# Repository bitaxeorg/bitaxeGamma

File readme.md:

```
Open Source is Intrinsic to Bitcoin
```
# The bitaxeGamma
bitaxe is a fully open source Bitcoin ASIC miner aimed at decentralizing mining. bitaxeGamma is the 5th major revision of the bitaxe that now includes the BM1370 ASIC from the Antminer S21 Pro

## Goals
- **Easy**: Just plug it in and mine Bitcoin over WiFi. No external computer needed.
- **Practical**: low cost, low noise, low power, low maintenance. You can run this at home.
- **ASIC Power**: High efficiency and hashrate, based on the latest and greatest Application Specific Integrated Circuits.
- **Versatile**: Mine to any StratumV1 pool, Lottery mine, Solo mine, Or hack it to do whatever you want.
- **Bitcoin Ethos**: Fully open source, permissionless and decentralized to support the worldwide freedom money.

## ASIC
At the heart of the bitaxeGamma is a BM1370 Bitcoin mining ASIC from the Antminer S21 Pro from Bitmain. It's not open source.

- Bitmain claims the BM1370 has 15 J/TH efficiency. We can get pretty close to that with the BitaxeGamma
- The Antminer S21 Pro has a nominal hashrate of 234 TH/s. There are 3 hashboards with 65 chips each, for a total of 195 chips. The bitaxeGamma has a single one of these chips. That means _about_ 1.2 TH/s per bitaxeGamma. Initial testing looks good!
- The BM1370 is brand new and isn't available individually yet. The best place to get these chips is right out of a S21 Pro.
- The BM1370 has a different footprint and pinout from the BM1368, BM1366, BM1397 and BM1387 in previous bitaxe.

## Current Status
- BitaxeGamma 600 is working well and has been released!
- In addition to higher hashrate, the Gamma also uses more power. Please pay attention to hash frequency and voltage settings as it's much easier to overheat, especially when using the stock heatsink and fan.
- BM1370 firmware support has been added to [esp-miner](https://github.com/skot/esp-miner)
- Be sure to check the [HW issues](https://github.com/skot/bitaxe/issues) for known bugs, reworks and errata.
- This is an _advanced_ build! You can do it, but if you're not looking for a project, it might be best to buy one pre-assembled from one of the [many sellers](https://bitaxe.org/legit.html). Check [Skot's method](assembly.md) of hand assembling PCBs.

## PCB Hardware
This repo contains all of the design files for the PCB. [KiCAD](https://www.kicad.org/) software is used. There is a BOM file for all of the components that get soldered to the PCB. 

- Order PCBs from your favorite PCB shop, like [JLCPCB](https://jlcpcb.com), [SeeedStudio](https://www.seeedstudio.com/fusion_pcb.html), or [PCBWay](https://www.pcbway.com)
    - Gerbers are in the `Manufacturing Files` dir. PCBs are 4-layer, 6mil trace/space and 0.3mm hole compatible. 1oz outer / 0.5oz inner layer thickness works well.
    - Make sure to order stencils too. These are the "paste" layers in the gerbers folder. one for top and one for bottom.
- All PCB parts except the ASIC are available from [DigiKey](https://www.digikey.com/en/products) and others. You can find Digikey part numbers on the DK tab of the BOM

## Extra Hardware
There are a few other hardware components that are needed for a complete bitaxe.

- **Heatsink**
	- [40x40mm heatsink and 5V fan](https://www.aliexpress.com/item/2251832861666365.html) from a random AliExpress seller. The fans are crap, but the heatsinks are good.  
- **Fan**
	- You **must** have active cooling on the bitaxe. The heatsink alone is not enough.
	- The Bitaxe has a connector for a 4pin, 5V PWM fan. 40mm square, 20mm thick fans work nicely with the suggested heatsink. Make sure to get a 5V fan! 12V spin, but slowly overheating your Bitaxe..
	- Upgrade your fan with the [Noctua NF-A4x10](https://noctua.at/en/nf-a4x10-5v-pwm) 5V 4-Pin fan for a much more pleasant experience.
- **Thermal compound**
	- Use a good quality thermal compound between the heatsink and ASIC. [Thermal Grizzly Kryonaut](https://www.amazon.com/Thermal-Grizzly-Kryonaut-Grease-Paste/dp/B011F7W3LU) has been known to work well.  
- **Display**
	- Supports 0.91" SSD1306-based I2C OLED Module. [Example Amazon seller](https://www.amazon.com/gp/product/B08ZY4YBHL). Make sure to get the male pins to interface with the Bitaxe PCB. 
- **Power Supply**
	- **5V DC Only!** Anything else will damage the Bitaxe. Be careful and double-check your power supply is 5V. Many other voltage power supplies use the same connector.
	- The power supply needs to supply in excess of 4A (20W) and not drop below 5V. Often times you have to use a power supply rated for 25-30W to get this!
 		- The [Meanwell GST60A05-P1J](https://www.digikey.com/en/products/detail/mean-well-usa-inc/GST60A05-P1J/7703709) at 30 Watts is the cadillac of 5V PSUs and is working well with the Gamma.  
	- The bitaxe uses a 5.5x2.1mm, center-positive barrel jack. 5.5x2.5mm plugs have been known to work.
- **Stand**
	- The PCB has corner mounting holes. You're going to want a stand to mount your Bitaxe. Many excellent 3D printed designs are available.

## Firmware
- The [ESP-Miner](https://github.com/skot/ESP-Miner) has initial support for the BM1370 ASIC. Improvements are ongoing.

### ESP32 Programming Requirements
- As of the bitaxeUltra, all ESP32 programming is done through a USB-C cable and connector on the bitaxe. See [ESP-Miner](https://github.com/skot/ESP-Miner) for more details.

## More Information
- Project page at [bitaxe.org](https://bitaxe.org)
- [Open Source Miners United](discord.gg/osmu) Discord chat
- [building.md](building.md) for PCB ordering tips
- [assembly.md](assembly.md) for assembly tips

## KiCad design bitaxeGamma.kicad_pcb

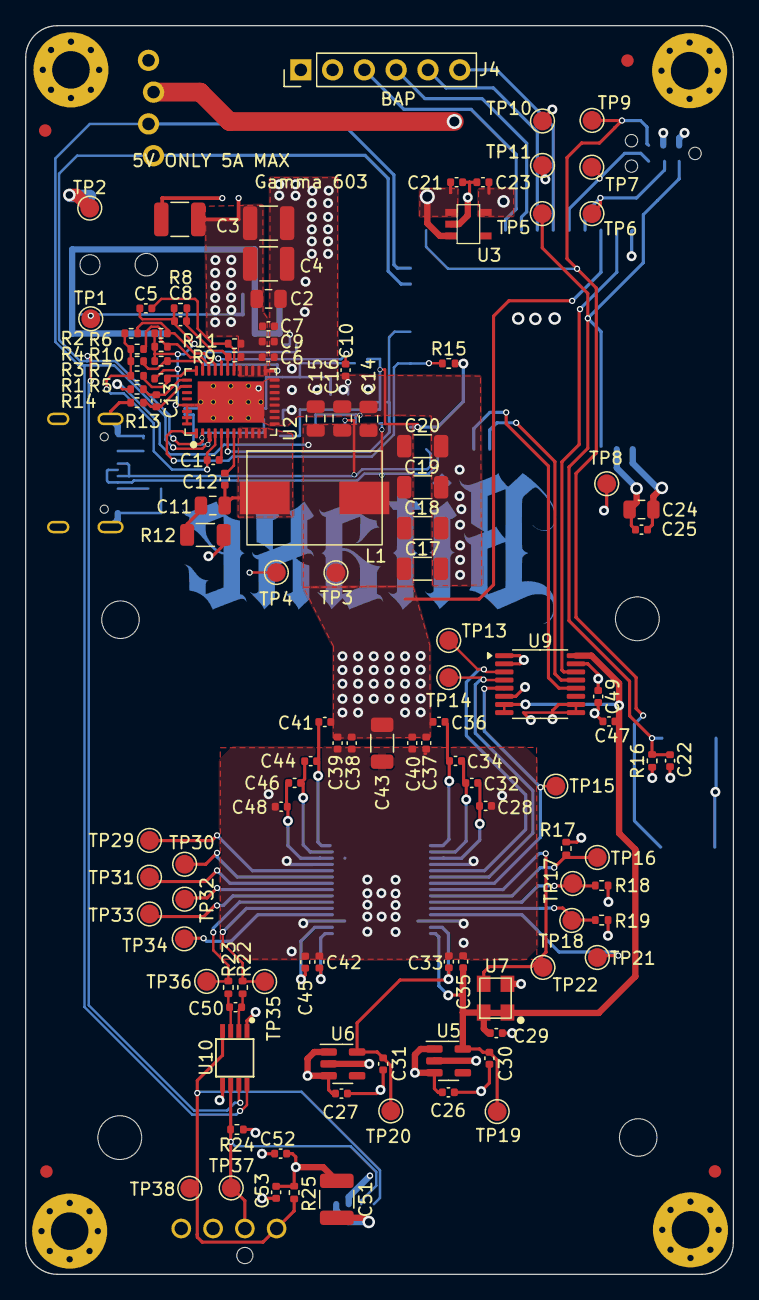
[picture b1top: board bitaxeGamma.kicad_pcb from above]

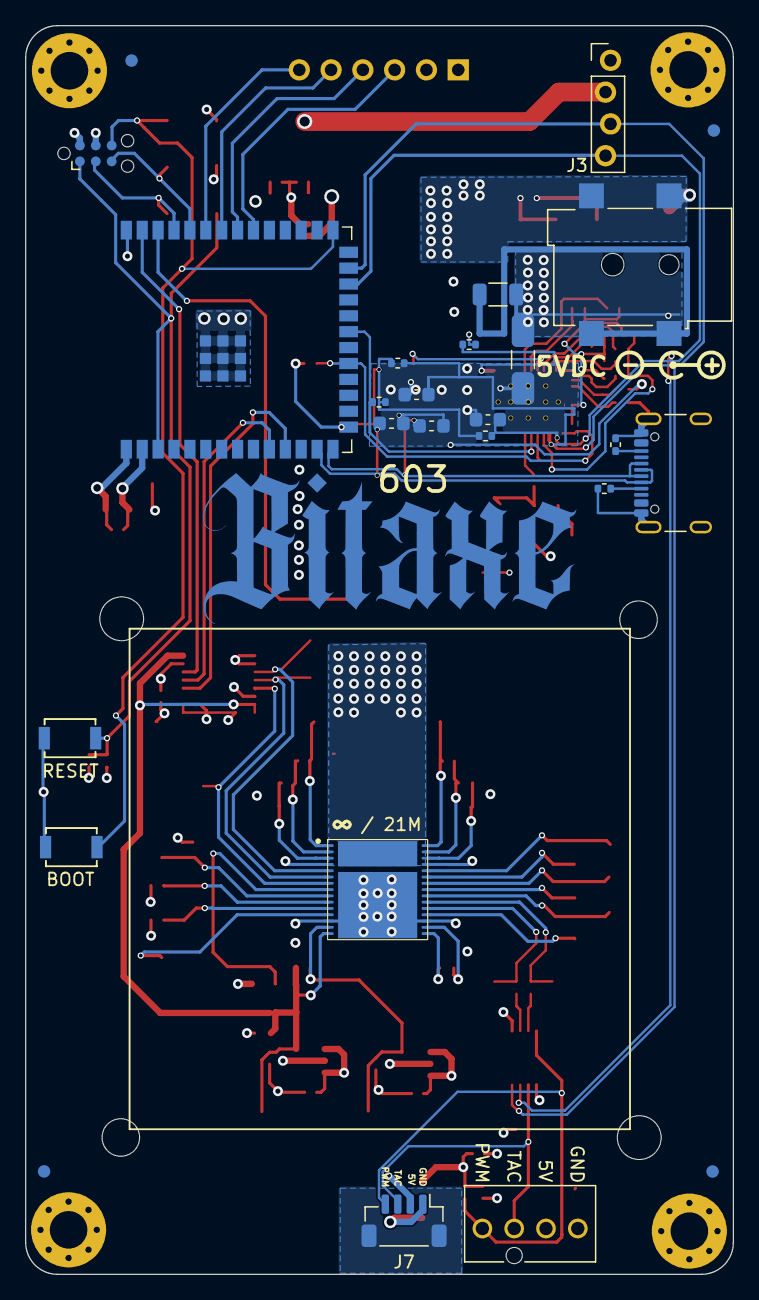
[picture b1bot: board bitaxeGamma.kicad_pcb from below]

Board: 4 copper layers, 56.5 x 99.8 mm, 157 parts (27 on the bottom side), 67 nets.

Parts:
C1, C5, C7, C21, C22, C23, C26, C27, C28, C30, C31, C32, C33, C34, C35, C36, C39, C40, C41, C42, C44, C45, C46, C48: 1uF; C_0402_1005Metric
C2, C24: 10uF; C_0805_2012Metric
C3, C4, C51: 47uF; C_1210_3225Metric
C6: 4700pF; C_0402_1005Metric
C8, C12, C25, C29, C37, C38, C47, C49, C52, C53, C62: 0.1uF; C_0402_1005Metric
C9: 2200pF; C_0402_1005Metric
C10: 4.7uF; C_0402_1005Metric
C11: 1000pF; C_0805_2012Metric
C13: 100pF; C_0402_1005Metric
C14, C15, C16: 22uF; C_0805_2012Metric
C17, C18, C19, C20, C43: 100uF; C_1206_3216Metric
C50: 470pF; C_0402_1005Metric
C60: 100uF; C_1210_3225Metric
D1: SMAJ5.0A; D_SMA
D2, D5: PESD5V0S1BL; D_SOD-323
D3, D4: PESD3V3S1BL; D_SOD-323
F1: 5A; Fuse_1206_3216Metric
FID1, FID2, FID3, FID4, FID5, FID6, FID7, FID8: Fiducial; Fiducial_1mm_Mask2mm
H1, H2, H3, H4: MountingHole_Pad; MountingHole_3mm_Pad_Via
H5, H6, H7, H8: MountingHole; MountingHole_3.5mm
J1: 54-00164; TENSILITY_54-00164
J2: TC2030-IDC; Tag-Connect_TC2030-IDC-NL_2x03_P1.27mm_Vertical
J3: Conn_01x04; PinHeader_1x04_P2.54mm_Vertical_shifted
J4: Conn_01x06; PinHeader_1x06_P2.54mm_Vertical
J5: USB_C_Receptacle_USB2.0; USB_C_Receptacle_GCT_USB4105-xx-A
J6: Conn_01x04; 470531000
J7: Conn_01x04; JST_SH_BM04B-SRSS-TB_1x04-1MP_P1.00mm_Vertical
L1: 300nH; SLC1175-271MEC_COC
R1: 8.25k; R_0402_1005Metric
R2, R3, R4, R7: R_0402_1005Metric
R5: 14.7k; R_0402_1005Metric
R6: 0; R_0402_1005Metric
R8: 3.74k; R_0402_1005Metric
R9: 11.8k; R_0402_1005Metric
R10: 68.1k; R_0402_1005Metric
R11: 10; R_0402_1005Metric
R12: 1; R_1206_3216Metric
R13, R14: 49.9; R_0402_1005Metric
R15, R16, R17, R25: 10k; R_0402_1005Metric
R18, R19: 1k; R_0402_1005Metric
R22, R23: 100; R_0402_1005Metric
R24: 5.6k; R_0402_1005Metric
R30, R31, R32: 4.7k; R_0402_1005Metric
R33, R34: 5.1k; R_0402_1005Metric
SW1, SW2: GT-TC029B-H025-L1N; SW_CS1213AGF260_CRS
T1: net-tie; NetTie-0.25mm
TP1, TP2, TP3, TP4, TP5, TP6, TP7, TP8, TP9, TP10, TP11, TP13, TP14, TP15, TP16, TP17, TP18, TP19, TP20, TP21, TP22, TP29, TP30, TP31, TP32, TP33, TP34, TP35, TP36, TP37, TP38: TestPoint; TestPoint_Pad_D1.5mm
U1: polarity
U2: TPS546D24ARVFR; LQFN40-CLIP
U3: RT9080-33GJ5
U4: ESP32-S3-WROOM-1
U5: MCP1824T-1202E/OT; SOT-23-5
U6: MCP1824T-0802E; SOT-23-5
U7: 25MHz; SMD3225-4P
U8: BM1370_mode1; BM1370
U9: SN74AVC4T774; TSSOP-16_4.4x5mm_P0.65mm
U10: EMC2101; TSSOP-8_3x3mm_P0.65mm

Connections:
/3V3: C23.1, C24.1, C25.1, C49.1, J2.2, J3.2, R15.2, R16.1, R24.2, R30.2, R31.2, R32.2, TP8.1, TP11.1, U3.5 (VOUT), U4.2 (3V3), U4.15 (GPIO3/TOUCH3/ADC1_CH2*), U9.15 (VCCB), U10.1 (VDD)
/5V: C2.1, C3.1, C4.1, C6.1, C7.1, C9.1, C21.1, C26.1, C27.1, C51.1, C52.1, C53.1, C60.1, C62.1, D1.1, F1.2, J4.1, J6.2, J7.2, R9.1, R11.1, R25.2, TP1.1, U2.21 (PVIN), U2.22 (PVIN), U2.23 (PVIN), U2.24 (PVIN), U2.25 (PVIN), U3.1 (VIN), U3.3 (EN), U5.1 (VIN), U5.3 (EN), U6.1 (VIN), U6.3 (EN)
/BM1370/0V8: C31.1, C33.1, TP20.1, U6.5 (VOUT), U8.14 (VDDIO_08_0)
/BM1370/1V2: C29.2, C30.1, C35.1, C47.1, TP19.1, U5.5 (VOUT), U7.1 (EN), U7.4 (VIN), U8.15 (VDDIO_12_0), U9.7 (DIR3), U9.8 (DIR4), U9.16 (VCCA)
/BM1370/BI: R17.2, TP16.1, U8.9 (BI)
/BM1370/BO: TP33.1, U8.22 (BO)
/BM1370/CI: TP14.1, U8.6 (CI), U9.4 (A2)
/BM1370/CLKI: TP22.1, U7.3 (OUT), U8.8 (CLKI)
/BM1370/CLKO: TP32.1, U8.23 (CLKO)
/BM1370/CO: TP30.1, U8.25 (CO)
/BM1370/NRSTO: TP29.1, U8.26 (NRSTO)
/BM1370/PIN_MODE: TP34.1, U8.19 (PIN_MODE)
/BM1370/RI: TP31.1, U8.24 (RI)
/BM1370/RO: TP15.1, U8.7 (RO), U9.5 (A3)
/BM1370/RST_N: TP13.1, U8.5 (NRSTI), U9.3 (A1)
/BM1370/VDD1_0: C34.2, C36.1, U8.1 (VDD3_0)
/BM1370/VDD1_1: C41.2, C44.1, U8.30 (VDD3_1)
/BM1370/VDD2_0: C32.2, C34.1, U8.2 (VDD2_0)
/BM1370/VDD2_1: C44.2, C46.1, U8.29 (VDD2_1)
/BM1370/VDD3_0: C28.2, C32.1, U8.3 (VDD1_0)
/BM1370/VDD3_1: C46.2, C48.1, U8.28 (VDD1_1)
/ESP32/EN: C22.1, J2.1, R16.2, SW1.2, TP5.1, U4.3 (EN)
/ESP32/IO0: J2.6, SW2.2, TP9.1, U4.27 (GPIO0/BOOT*)
/ESP32/P_RX: J2.5, TP7.1, U4.36 (U0RXD/GPIO44/CLK_OUT2)
/ESP32/P_TX: J2.3, TP6.1, U4.37 (U0TXD/GPIO43/CLK_OUT1)
/ESP32/USB_D+: D2.1, J5.A6 (D+), J5.B6 (D+), U4.14 (GPIO20/U1CTS/ADC2_CH9/CLK_OUT1/USB_D+)
/ESP32/USB_D-: D5.1, J5.A7 (D-), J5.B7 (D-), U4.13 (GPIO19/U1RTS/ADC2_CH8/CLK_OUT2/USB_D-)
/Fan/FAN_PWM: J6.4, J7.4, R25.1, TP38.1, U10.4 (FAN)
/Fan/FAN_TACH: J6.3, J7.3, R24.1, TP37.1, U10.6 (ALERT/TACH)
/Fan/TEMP_DN: C50.2, R22.1, U10.3 (DN)
/Fan/TEMP_DP: C50.1, R23.2, U10.2 (DP)
/Fan/TEMP_N: R22.2, TP36.1, U8.21 (TEMP_N)
/Fan/TEMP_P: R23.1, TP35.1, U8.20 (TEMP_P)
/Power/AGND: C5.1, C8.2, R5.1, R6.2, R7.2, R8.2, R10.2, T1.1, U2.37 (AGND), U2.38 (SYNC), U2.39 (BCX_CLK), U2.40 (BCX_DAT)
/Power/PGOOD: R15.1, U2.1 (PGD), U4.19 (GPIO11/TOUCH11/ADC2_CH0/FSPID/FSPIIO5/S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)
/Power/PMB_ALRT: R32.1, U2.6 (SMB_ALRT), U4.21 (GPIO13/TOUCH13/ADC2_CH2/FSPIQ/FSPIIO7/S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)
/Power/SW: C11.2, C12.2, L1.1, U2.8 (SW), U2.9 (SW), U2.10 (SW), U2.11 (SW), U2.12 (SW)
/RST: U4.39 (GPIO1/TOUCH1/ADC1_CH0), U9.14 (B1)
/RX: U4.11 (GPIO18/U1RXD/ADC2_CH7/CLK_OUT3), U9.12 (B3)
/SCL: D4.1, J3.3, R31.1, U2.3 (PMB_CLK), U4.25 (GPIO48/SPICLK_N/SUBSPICLK_N_DIFF), U10.8 (SMCLK)
/SDA: D3.1, J3.4, R30.1, U2.2 (PMB_DATA), U4.24 (GPIO47/SPICLK_P/SUBSPICLK_P_DIFF), U10.7 (SMDATA)
/TX: U4.10 (GPIO17/U1TXD/ADC2_CH6), U9.13 (B2)
/VDD: C14.1, C15.1, C16.1, C17.1, C18.1, C19.1, C20.1, C36.2, C37.1, C38.1, C39.1, C40.1, C41.1, C43.1, L1.2, R14.1, TP3.1, U4.38 (GPIO2/TOUCH2/ADC1_CH1), U8.31 (VDD)
GND: C2.2, C3.2, C4.2, C6.2, C7.2, C9.2, C10.2, C14.2, C15.2, C16.2, C17.2, C18.2, C19.2, C20.2, C21.2, C22.2, C23.2, C24.2, C25.2, C26.2, C27.2, C28.1, C29.1, C30.2, C31.2, C33.2, C35.2, C37.2, C38.2, C39.2, C40.2, C42.2, C43.2, C45.2, C47.2, C48.2, C49.2, C51.2, C52.2, C53.2, C60.2, C62.2, D1.2, D2.2, D3.2, D4.2, D5.2, H1.1, H2.1, H3.1, H4.1, J1.2, J1.3, J2.4, J3.1, J4.2, J5.A1 (GND), J5.B1 (GND), J5.S1 (SHIELD), J6.1, J7.1, R12.1, R13.2, R17.1, R18.1, R19.1, R33.2, R34.2, SW1.1, SW2.1, T1.2, TP2.1, TP4.1, TP10.1, U2.13 (PGND), U2.14 (PGND), U2.15 (PGND), U2.16 (PGND), U2.17 (PGND), U2.18 (PGND), U2.19 (PGND), U2.20 (PGND), U2.41 (PAD), U3.2 (GND), U4.1 (GND), U4.40 (GND), U4.41 (GND), U5.2 (GND), U6.2 (GND), U7.2 (GND), U8.4 (VSS), U8.13 (PLL_VSS), U8.18 (VSS), U8.27 (VSS), U8.32 (VSS), U9.1 (DIR1), U9.2 (DIR2), U9.6 (A4), U9.9 (OE), U9.10 (GND), U10.5 (GND)
unnamed: C11.1, R12.2
unnamed: F1.1, J1.1
unnamed: J4.3, U4.32 (MTCK/GPIO39/CLK_OUT3/SUBSPICS1)
unnamed: J4.4, U4.33 (MTDO/GPIO40/CLK_OUT2)
unnamed: J4.5, U4.34 (MTDI/GPIO41/CLK_OUT1)
unnamed: J4.6, U4.35 (MTMS/GPIO42)
unnamed: R3.2, R7.1, U2.31 (ADRSEL)
unnamed: C5.2, R11.2, U2.26 (AVIN)
unnamed: C12.1, U2.7 (BOOT)
unnamed: C1.2, R1.1, R2.1, R3.1, R4.1, U2.4 (BP1V5)
unnamed: C1.1, U2.5 (DRTN)
unnamed: C8.1, R8.1, R9.2, U2.27 (EN/UVLO)
unnamed: C13.2, R13.1, U2.34 (GOSNS)
unnamed: R1.2, R5.2, U2.32 (MSEL1)
unnamed: R2.2, R6.1, U2.29 (MSEL2)
unnamed: C10.1, U2.28 (VDD5)
unnamed: C13.1, R14.2, U2.33 (VOSNS)
unnamed: R4.2, R10.1, U2.30 (VSEL)
unnamed: TP21.1, U8.12 (INV_CLKO)
unnamed: R19.2, TP18.1, U8.11 (LITE_PAD)
unnamed: R18.2, TP17.1, U8.10 (ROSC_SEL)
unnamed: C45.1, U8.17 (VDDIO_08_1)
unnamed: C42.1, U8.16 (VDDIO_12_1)

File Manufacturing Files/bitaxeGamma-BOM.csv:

Qty,Reference,Value,PARTNO,DK,LCSC
1,R6,0,RC0402JR-070RL,311-0.0JRCT-ND,
1,C13,100pF,885012005013,732-7431-1-ND,
1,C50,470pF,CL05B471KB5NNNC,1276-1566-1-ND,
1,C11,1000pF,CC0805KRX7R9BB102,311-1127-1-ND,
7,C8 C12 C29 C47 C49 C52 C53,0.1uF,CL05A104KO5NNNC,1276-1234-1-ND,
1,L1,300nH,104CDMCCDS-R30MC,,
21,C1 C5 C21 C22 C23 C26 C27 C28 C30 C31 C32 C33 C34 C35 C36 C41 C42 C44 C45 C46 C48,1uF,EMK105BJ105MV-F,587-5514-1-ND,
3,C6 C7 C9,10uF,GRM188R61E106KA73D,490-18214-1-ND,
10,C2 C3 C4 C17 C18 C19 C20 C43 C51 C54,100uF,CL31A107MQHNNNE,1276-1782-1-ND,
1,R12,1,CSR1206FT1R00,CSR1206FT1R00CT-ND,
1,R11,10,RC0402FR-0710RL,311-10.0LRCT-ND,
2,R13 R14,49.9,RC0402FR-0749R9L,311-49.9LRCT-ND,
2,R22 R23,100,RC0402FR-07100RL,311-100LRCT-ND,
1,R19,1k,RC0402FR-071KL,311-1.00KLRCT-ND,
1,R8,3.74k,RC0402FR-073K74L,311-3.74KLRCT-ND,
1,R24,5.6k,RC0402FR-135K6L,13-RC0402FR-135K6LCT-ND,
1,R1,8.25k,RC0402FR-078K25L,311-8.25KLRCT-ND,
4,R15 R16 R17 R25,10k,RC0402JR-0710KL,311-10KJRCT-ND,
1,R9,11.8k,RC0402FR-0711K8L,YAG2958CT-ND,
1,R5,14.7k,RC0402FR-0714K7L,YAG2984CT-ND,
1,R10,68.1k,RC0402FR-0768K1L,YAG3213CT-ND,
1,U7,25MHz,SX3M25.000E20F30THN,5852-SX3M25.000E20F30THNTR-ND,C5137262
1,J1,54-00164,54-00164,839-54-00164CT-ND,C431534
1,U8,BM1370_mode1,,,
1,J6,Conn_01x04,0470531000,WM4330-ND,
1,J7,Conn_01x04,,,
1,U10,EMC2101,EMC2101-R-ACZL-TR,EMC2101-R-ACZL-CT-ND,
1,U4,ESP32-S3-WROOM-1,ESP32-S3-WROOM-1-N16R8,1965-ESP32-S3-WROOM-1-N16R8CT-ND,
2,SW1 SW2,GT-TC029B-H025-L1N,CS1213AGF260,2449-CS1213AGF260CT-ND,
1,U6,MCP1824T-0802E,MCP1824T-0802E/OT,MCP1824T-0802E/OTCT-ND,
1,U5,MCP1824T-1202E/OT,MCP1824T-1202E/OT,MCP1824T-1202E/OTCT-ND,
1,U3,RT9080-33GJ5,RT9080-33GJ5,1028-1509-1-ND,
1,U9,SN74AVC4T774,SN74AVC4T774PWR,296-24739-1-ND,
1,U2,TPS546D24ARVFR,TPS546D24ARVFR,296-TPS546D24ARVFRCT-ND,
1,J5,USB_C_Receptacle_USB2.0,USB4105-GF-A,2073-USB4105-GF-ACT-ND,

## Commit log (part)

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2025-01-21 added alternate part number for the 25MHz ASIC oscillator
2025-01-25 Cleaned up zones, increased vdd trace width
2025-01-25 mounting holes to 3mm
2025-01-25 lots of misc
2025-01-25 more input vias
2025-01-25 tps546 is smd
2025-01-25 refill zones
2025-01-25 gerbers
2025-01-28 inductor change
2025-02-02 Create Kaka
    For gerber file
2025-02-02 Create Kaka
2025-02-14 layout
2025-02-14 DRC/layout
2025-03-05 Fix BM17 footprint
2025-03-06 update footprint
2025-03-16 update to KiCad v9
2025-03-16 remove unused DNP column from BOM
2025-03-16 602 final
2025-03-17 added pullup resistors for #25
2025-03-18 Revert "added pullup resistors for #25"
    This reverts commit 91572af801fdd590416a5d3df79444bb16faa4cf.
2025-04-24 exported BOM. Updated KiCad files to v9
2025-04-24 BOM cleanup
2025-04-24 removed old BOM. added iBOM
2025-04-24 pcb sync
2025-04-29 remove incorrect J3 partno for #28. removed random dust from mounting hole positions for #32. bumped version to 603. added NRSTO pulldown. added NRSTI pulldown for #36. removed old manufacturing file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
2025-04-29 added USB ID pulldown resistors for #37
2025-06-07 fix: adjust vdd route
2025-06-09 remove old outdated gerbers
2025-06-19 removed unused fan header
2025-06-19 silkscreen, drc
2025-08-31 Fix Discord Link
    Improper/Broken Link. Fixed for OSMU Discord
2025-09-15 Fixed KiCAD link
    Fixed KiCAD link to kicad.org
2025-12-18 init
2025-12-27 imporved TPS546 thermal vias
2026-02-17 add 3d models
2026-02-17 update worksheet
2026-05-30 Fix spelling error in readme.md
    Fixed spelling error in readme. "attemtion" was corrected to "attention"
